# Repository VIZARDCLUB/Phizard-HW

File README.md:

# Phizard-HW

The Phizard board is licensed under CERN Open Hardware Licence Version 2 - Strongly Reciprocal.  
This means that any changes made to the board should be made public and CHANGES.txt be updated to reflect said changes.  

The Phizard Link-V board is licensed under GPL-3.0 licence.  

Phizard has some added features based on PhobGCC 2.0.5.  
Currently works with [PhoZL](https://github.com/sean44104/PhoZL) firmware.  

# CHANGES.txt
- Original pad footprint for ABXY. Support 2pin DIP switches. Added holes for D2LS switches.  
- Original pad footprint for D-pad. Support SMD tact switches, D2LS switches and 2pin DIP switches.  
- Added thin tactile switch support to the START button.  
- Swap USB connecter to USB-C.  
- Added ZL button connected to GPIO12. Works with PhoZL firmware.  
- Fixed the Z/ZL footprint to fit right angle mouse switches.  
- Added breakout pad for Dup and Dleft for SoreiruFactory's Double LR Trigger.
- Added a 22ohm resister and a pad for 3.3V cell rumble.  
- Added Phizard Link-V based on OlyU-V. This supports Phob vision output. (I will make an adapter for it in the future.)
- PH connector can be used for LR pad without shell trimming

# Parts example
[H5.2mm Square micro switch](https://a.aliexpress.com/_on09e08) for ABXY and D-pad  
[D2LS-11](https://mou.sr/3ILtBsM) and the other switches that uses the same footprint for ABXY and Dpad  
[SKRRAAE010](https://mou.sr/3PtAZNg) and GBASP start button rubber for start (The edited shell will be published after tested)  

# Credit
## Main board
https://github.com/PhobGCC/PhobGCCv2-HW  
https://github.com/sean44104/phozl  

## USB features
https://github.com/Crane1195/Model-U  
https://github.com/sean44104/OlyU  
https://github.com/rana-sylvatica/OlyU-V

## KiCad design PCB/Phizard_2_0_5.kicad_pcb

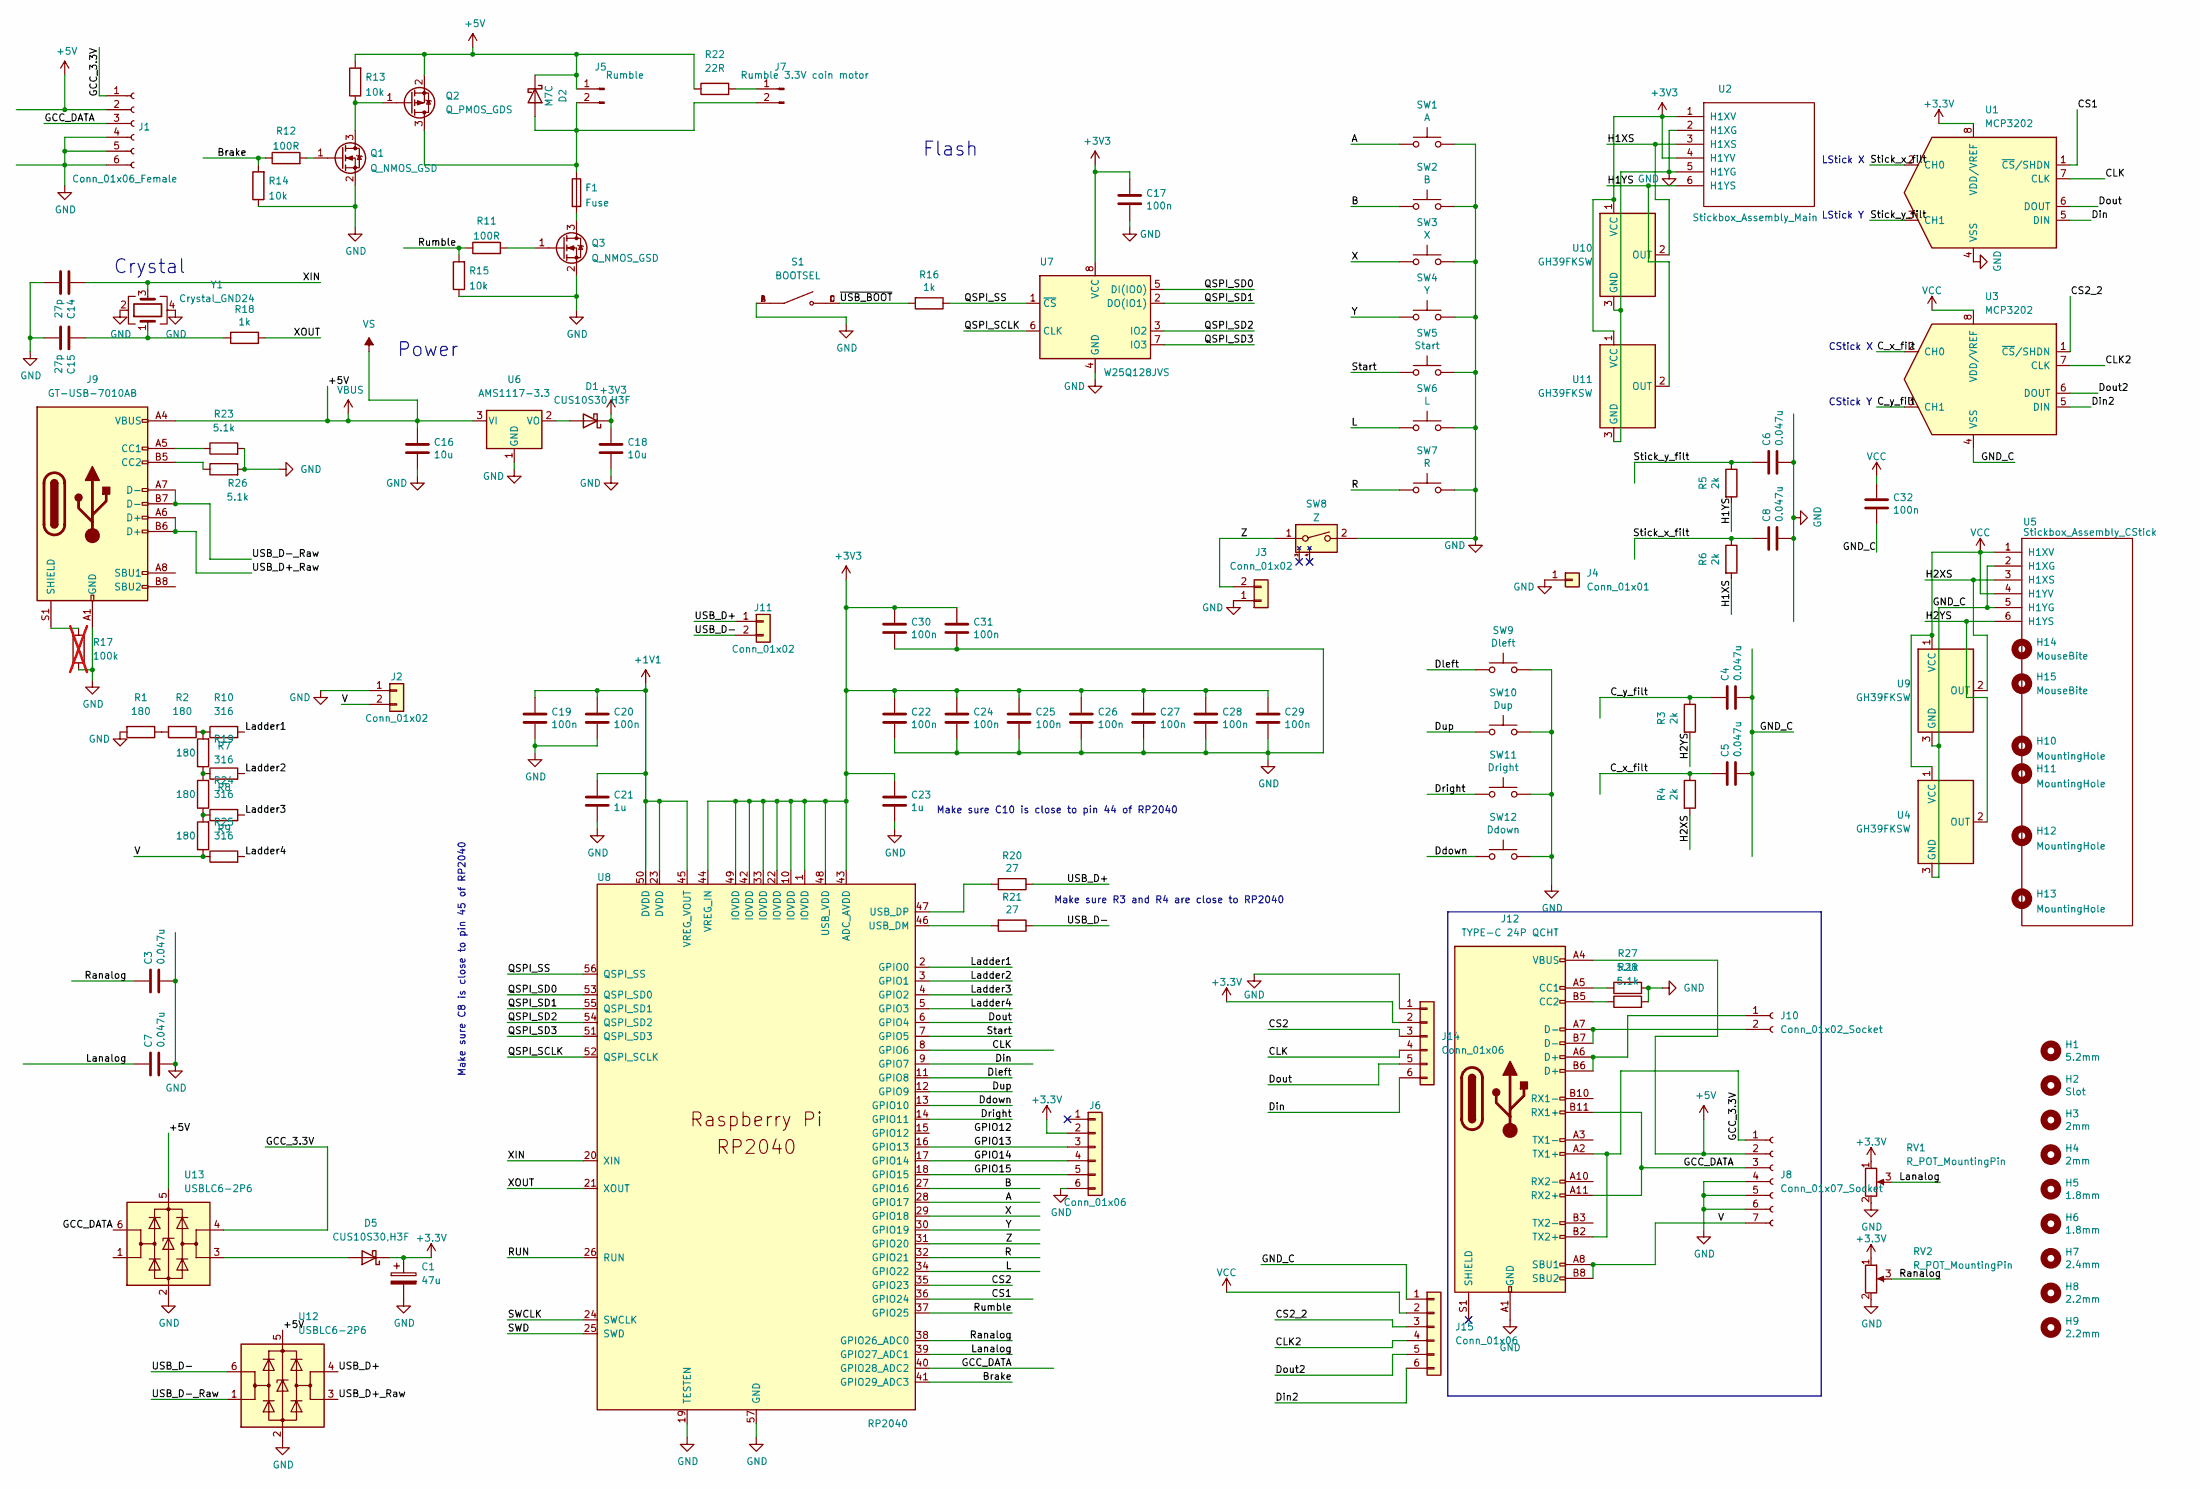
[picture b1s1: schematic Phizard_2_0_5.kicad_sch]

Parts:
C1: 47u; CP_EIA-3528-12_Kemet-T_Pad1.50x2.35mm_HandSolder; LCSC C136751
C3, C4, C5, C6, C7, C8: 0.047u; C_0603_HandSoldering; LCSC C1622
C14, C15: 27p; C_0402_1005Metric; LCSC C1557
C16, C18: 10u; C_0805_2012Metric; LCSC C15850
C17, C19, C20, C22, C24, C25, C26, C27, C28, C29, C30, C31, C32: 100n; C_0402_1005Metric; LCSC C1525
C21, C23: 1u; C_0402_1005Metric; LCSC C52923
D1, D5: CUS10S30,H3F; D_SOD-323; LCSC C146335
D2: M7C; D_SOD-123; LCSC C8598
F1: Fuse; Fuse_1206_3216Metric; LCSC C69680
H1: 5.2mm; MountingHole_5.2mm
H2: Slot
H3, H4: 2mm; MountingHole_2.0mm
H5, H6: 1.8mm; MountingHole_1.8mm
H7: 2.4mm; MountingHole_2.4mm
H8, H9: 2.2mm; MountingHole_2.2mm
H10: MountingHole; MountingHole_1.8mm
H11: MountingHole; MountingHole_5.2mm
H12, H13: MountingHole; MountingHole_2.0mm
H14: MouseBite; breakaway-mousebites-double-v2-small
H15: MouseBite; breakaway-mousebites-double-v2-large
J1: Conn_01x06_Female; GCC_Header_Straight_1x06_Pitch2.00mm
J2, J11: Conn_01x02; PinHeader_1x02_P2.00mm_Vertical
J3: Conn_01x02; PinHeader_1x02_P2.00mm_Horizontal
J4: Conn_01x01; PinHeader_1x01_P2.54mm_Vertical
J5: Rumble; rumble_pins
J6, J14, J15: Conn_01x06; PinSocket_1x06_P2.00mm_Vertical
J7: Rumble 3.3V coin motor; rumble_pins
J8: Conn_01x07_Socket
J9: GT-USB-7010AB; USB_C_Receptacle_G-Switch_GT-USB-7010ASV; LCSC C963412
J10: Conn_01x02_Socket
J12: TYPE-C 24P QCHT; LCSC C456013
Q1, Q3: Q_NMOS_GSD; SOT-23; LCSC C20917
Q2: Q_PMOS_GDS; SOT-23; LCSC C15127
R1, R2, R7, R8, R9: 180; R_0402_1005Metric; LCSC C38941
R3, R4, R5, R6: 2k; R_0603_1608Metric_Pad0.98x0.95mm_HandSolder; LCSC C22975
R10, R19, R24, R25: 316; R_0402_1005Metric; LCSC C159037
R11, R12: 100R; R_0603_1608Metric_Pad0.98x0.95mm_HandSolder; LCSC C22775
R13, R14, R15: 10k; R_0603_1608Metric_Pad0.98x0.95mm_HandSolder; LCSC C25804
R16, R18: 1k; C_0402_1005Metric; LCSC C11702
R17: 100k; R_0603_1608Metric_Pad0.98x0.95mm_HandSolder; LCSC C25803; not fitted
R20, R21: 27; C_0402_1005Metric; LCSC C25100
R22: 22R; R_1206_3216Metric; LCSC C2845146
R23, R26, R27, R28: 5.1k; R_0402_1005Metric; LCSC C105872
RV1, RV2: R_POT_MountingPin; GCC_Slider
S1: BOOTSEL; SW_TS-1187A-B-A-B; PARTREV A0; LCSC C318884
SW1: A; ABXY_Contact_Omron_Switch_Circley
SW2: B; ABXY_Contact_Omron_Switch_Circley
SW3: X; ABXY_Contact_Omron_Switch_Circley
SW4: Y; ABXY_Contact_Omron_Switch_Circley
SW5: Start; Start_Contact
SW6: L; Pin_Header_Straight_1x02_Pitch2.54mm
SW7: R; Pin_Header_Straight_1x02_Pitch2.54mm
SW8: Z; Z_Switch_Edge_Omron
SW9: Dleft; Dpad_Contact_TL3315NF_2_ZigZag
SW10: Dup; Dpad_Contact_TL3315NF_2_ZigZag
SW11: Dright; Dpad_Contact_TL3315NF_2_ZigZag
SW12: Ddown; Dpad_Contact_TL3315NF_2_ZigZag
U1, U3: MCP3202; SOIC-8_3.9x4.9mm_P1.27mm; LCSC C56997
U2: Stickbox_Assembly_Main; GCC_Stickbox_Hall_Only
U4, U9, U10, U11: GH39FKSW; SOT-23; LCSC C266128
U5: Stickbox_Assembly_CStick; GCC_Stickbox_Hall_Only
U6: AMS1117-3.3; SOT-223-3_TabPin2; LCSC C6186
U7: W25Q128JVS; SOIC-8_5.23x5.23mm_P1.27mm; LCSC C97521
U8: RP2040; RP2040-QFN-56; LCSC C2040
U12, U13: USBLC6-2P6; SOT-666; LCSC C2827693
Y1: Crystal_GND24; Crystal_SMD_3225-4Pin_3.2x2.5mm; LCSC C403945

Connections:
+1V1: C19.1, C20.1, C21.1, U8.23 (DVDD), U8.45 (VREG_VOUT), U8.50 (DVDD)
+5V: C16.1, D2.1 (K), J1.2, J5.1, J8.2, J9.A4 (VBUS), J9.A9 (VBUS), J9.B4 (VBUS), J9.B9 (VBUS), J12.A4 (VBUS), J12.A9 (VBUS), J12.B4 (VBUS), J12.B9 (VBUS), Q2.2 (S), R13.2, R22.1, U6.3 (VI), U12.5 (VBUS), U13.5 (VBUS)
/A: SW1.1, U8.28 (GPIO17)
/B: SW2.1, U8.27 (GPIO16)
/Brake: R12.1, R14.2, U8.41 (GPIO29_ADC3)
/CLK: J14.4, U1.7 (CLK), U8.8 (GPIO6)
/CLK2: J15.4, U3.7 (CLK)
/CS1: U1.1 (~CS/SHDN), U8.36 (GPIO24)
/CS2: J14.3, U8.35 (GPIO23)
/CS2_2: J15.3, U3.1 (~CS/SHDN)
/C_x_filt: C5.1, R4.1, U3.2 (CH0)
/C_y_filt: C4.1, R3.1, U3.3 (CH1)
/Ddown: SW12.1, SW12.3, SW12.5, U8.13 (GPIO10)
/Din: J14.6, U1.5 (DIN), U8.9 (GPIO7)
/Din2: J15.6, U3.5 (DIN)
/Dleft: SW9.1, SW9.3, SW9.5, U8.11 (GPIO8)
/Dout: J14.5, U1.6 (DOUT), U8.6 (GPIO4)
/Dout2: J15.5, U3.6 (DOUT)
/Dright: SW11.1, SW11.3, SW11.5, U8.14 (GPIO11)
/Dup: SW10.1, SW10.3, SW10.5, U8.12 (GPIO9)
/GCC_3.3V: J1.1, J8.1, J12.A2 (TX1+), J12.B2 (TX2+), U13.4 (I/O2)
/GCC_DATA: J1.3, J8.3, J12.A11 (RX2+), J12.B11 (RX1+), U8.40 (GPIO28_ADC2), U13.6 (I/O1)
/GND_C: C4.2, C5.2, C32.2, J15.1, U3.4 (VSS), U4.3 (GND), U5.2 (H1XG), U5.5 (H1YG), U9.3 (GND)
/GPIO12: U8.15 (GPIO12); also elsewhere on the board
/GPIO13: J6.3, U8.16 (GPIO13)
/GPIO14: J6.4, U8.17 (GPIO14)
/GPIO15: J6.5, U8.18 (GPIO15)
/H1XS: R6.2, U2.3 (H1XS), U10.2 (OUT)
/H1YS: R5.2, U2.6 (H1YS), U11.2 (OUT)
/H2XS: R4.2, U5.3 (H1XS), U9.2 (OUT)
/H2YS: R3.2, U4.2 (OUT), U5.6 (H1YS)
/L: SW6.1, U8.34 (GPIO22)
/Ladder1: R10.2, U8.2 (GPIO0)
/Ladder2: R19.2, U8.3 (GPIO1)
/Ladder3: R24.2, U8.4 (GPIO2)
/Ladder4: R25.2, U8.5 (GPIO3)
/Lanalog: C7.1, RV1.3 (Signal), U8.39 (GPIO27_ADC1)
/QSPI_SCLK: U7.6 (CLK), U8.52 (QSPI_SCLK)
/QSPI_SD0: U7.5 (DI(IO0)), U8.53 (QSPI_SD0)
/QSPI_SD1: U7.2 (DO(IO1)), U8.55 (QSPI_SD1)
/QSPI_SD2: U7.3 (IO2), U8.54 (QSPI_SD2)
/QSPI_SD3: U7.7 (IO3), U8.51 (QSPI_SD3)
/QSPI_SS: R16.1, U7.1 (~CS), U8.56 (QSPI_SS)
/R: SW7.1, U8.32 (GPIO21)
/RUN: U8.26 (RUN)
/Ranalog: C3.1, RV2.3 (Signal), U8.38 (GPIO26_ADC0)
/Rumble: R11.1, R15.2, U8.37 (GPIO25)
/SWCLK: U8.24 (SWCLK)
/SWD: U8.25 (SWD)
/Start: SW5.1, U8.7 (GPIO5)
/Stick_x_filt: C8.1, R6.1, U1.2 (CH0)
/Stick_y_filt: C6.1, R5.1, U1.3 (CH1)
/USB_D+_Raw: J9.A6 (D+), J9.B6 (D+), U12.3 (I/O2)
/USB_D-_Raw: J9.A7 (D-), J9.B7 (D-), U12.1 (I/O1)
/V: J1.7, J2.2, J8.7, J12.A8 (SBU1), J12.B8 (SBU2), R9.1, R25.1
/X: SW3.1, U8.29 (GPIO18)
/XIN: C14.1, U8.20 (XIN), Y1.3
/XOUT: R18.1, U8.21 (XOUT)
/Y: SW4.1, U8.30 (GPIO19)
/Z: J3.2, SW8.1, U8.31 (GPIO20)
/~USB_BOOT: R16.2, S1.C, S1.D
GND: C1.2, C3.2, C6.2, C7.2, C8.2, C14.2, C15.2, C16.2, C17.2, C18.2, C19.2, C20.2, C21.2, C22.2, C23.2, C24.2, C25.2, C26.2, C27.2, C28.2, C29.2, C30.2, C31.2, J1.4, J1.5, J1.6, J2.1, J3.1, J4.1, J6.6, J8.4, J8.5, J8.6, J9.A1 (GND), J9.A12 (GND), J9.B1 (GND), J9.B12 (GND), J12.A1 (GND), J12.A12 (GND), J12.B1 (GND), J12.B12 (GND), J14.1, Q1.2 (S), Q3.2 (S), R1.2, R14.1, R15.1, R17.2, R23.2, R26.2, R27.2, R28.2, RV1.2 (GND), RV2.2 (GND), S1.A, S1.B, SW1.2, SW2.2, SW3.2, SW4.2, SW5.2, SW6.2, SW7.2, SW8.2, SW9.2, SW9.4, SW9.6, SW10.2, SW10.4, SW10.6, SW11.2, SW11.4, SW11.6, SW12.2, SW12.4, SW12.6, U1.4 (VSS), U2.2 (H1XG), U2.5 (H1YG), U6.1 (GND), U7.4 (GND), U8.19 (TESTEN), U8.57 (GND), U10.3 (GND), U11.3 (GND), U12.2 (GND), U13.2 (GND), Y1.2, Y1.4; also elsewhere on the board
unnamed: C15.1, R18.2, Y1.1
unnamed: D1.2 (A), U6.2 (VO)
unnamed: D2.2 (A), F1.1, J5.2, J7.2, Q2.3 (D)
unnamed: D5.2 (A), U13.3 (I/O2)
unnamed: J7.1, R22.2
unnamed: J9.A5 (CC1), R23.1
unnamed: J9.B5 (CC2), R26.1
unnamed: J9.S1 (SHIELD), R17.1
unnamed: J12.A5 (CC1), R27.1
unnamed: J12.B5 (CC2), R28.1
unnamed: Q1.3 (D), Q2.1 (G), R13.1
unnamed: Q1.1 (G), R12.2
unnamed: F1.2, Q3.3 (D)
unnamed: Q3.1 (G), R11.2
unnamed: R1.1, R2.2
unnamed: R2.1, R7.2, R10.1
unnamed: R7.1, R8.2, R19.1
unnamed: R8.1, R9.2, R24.1
unnamed: R21.2, U8.46 (USB_DM)
unnamed: R20.2, U8.47 (USB_DP)
VCC: C32.1, J15.2, U3.8 (VDD/VREF), U4.1 (VCC), U5.1 (H1XV), U5.4 (H1YV), U9.1 (VCC)

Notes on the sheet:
Power
LStick Y
Make sure C10 is close to pin 44 of RP2040
CStick Y
Make sure R3 and R4 are close to RP2040
Make sure C8 is close to pin 45 of RP2040
Flash
Crystal
CStick X
LStick X

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
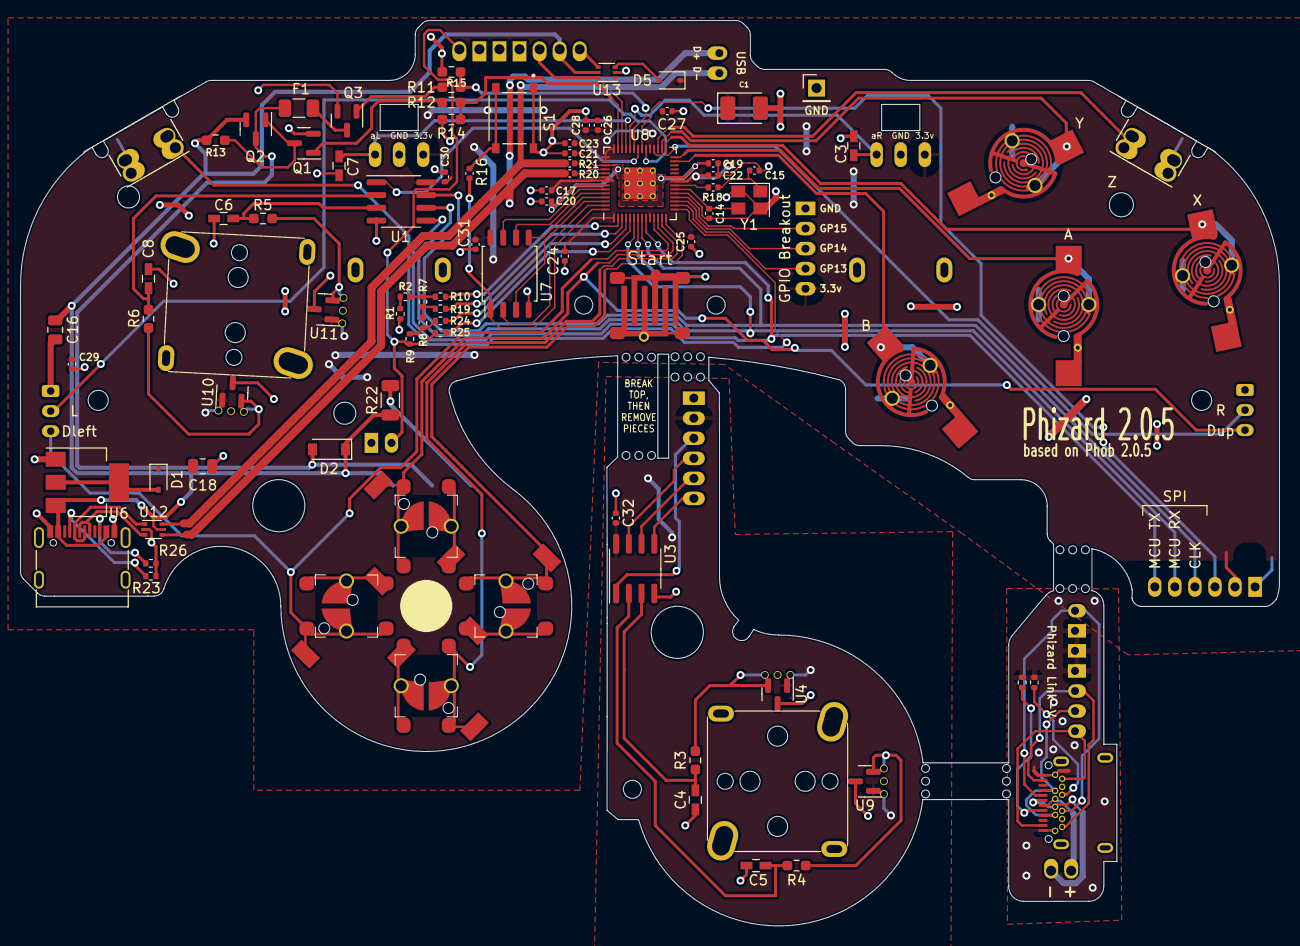
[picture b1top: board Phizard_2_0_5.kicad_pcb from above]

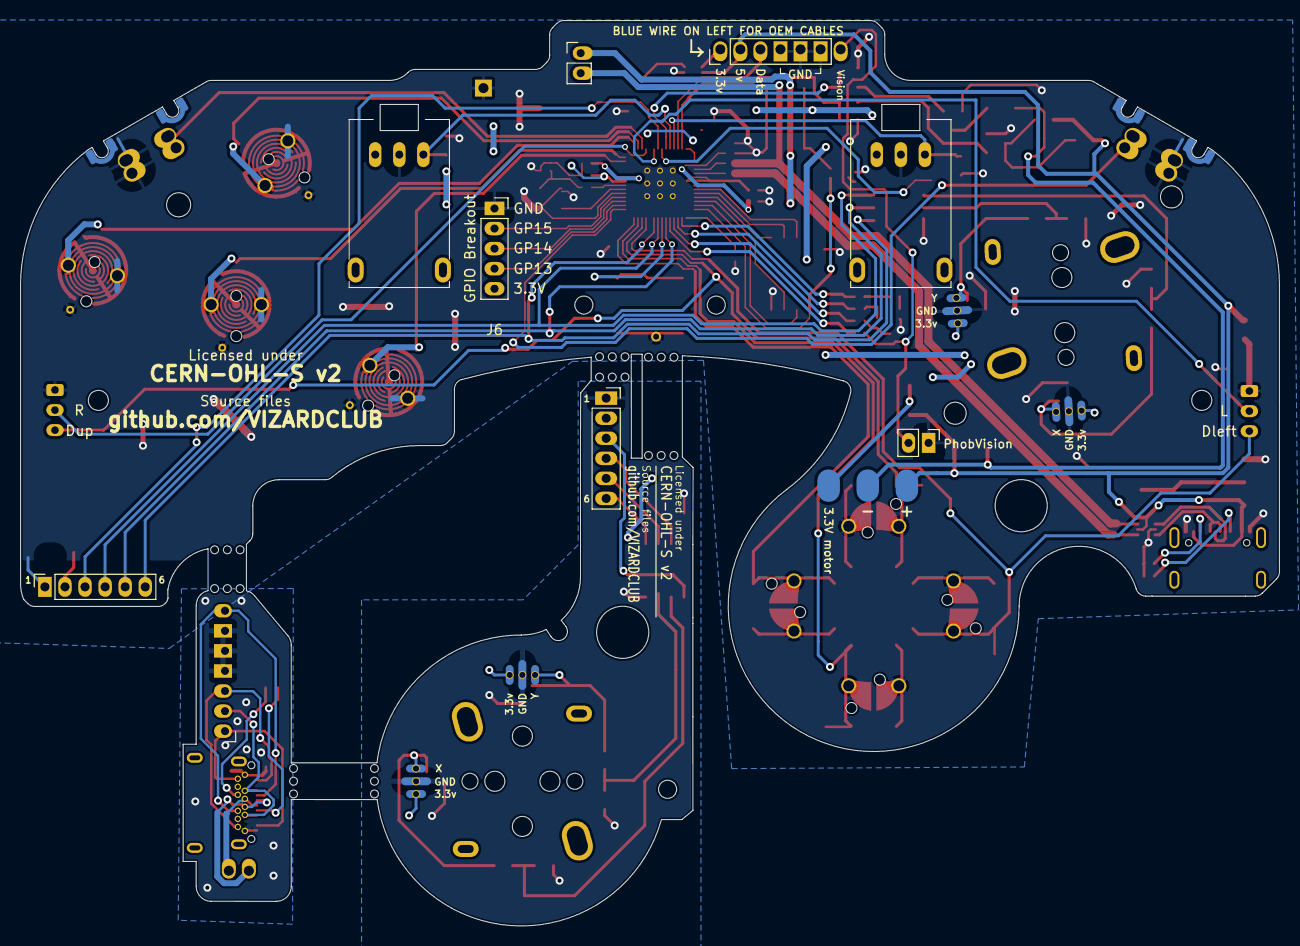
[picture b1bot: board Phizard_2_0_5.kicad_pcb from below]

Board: 2 copper layers, 125.5 x 90.3 mm, 122 parts (13 on the bottom side), 82 nets.

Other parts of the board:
H14#2, H14#3, H14#4, H14#5: MouseBite; breakaway-mousebites-double-v2-small
SW8#2: Z; Z_Switch_Edge_Omron

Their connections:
/GPIO12: SW8#2.2; also elsewhere on the board
GND: SW8#2.1; also elsewhere on the board

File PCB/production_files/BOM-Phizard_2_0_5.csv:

Comment,Designator,Footprint,LCSC
5.1k,"R23,R26,R27,R28",R_0402_1005Metric,C105872
1k,"R16,R18",C_0402_1005Metric,C11702
47u,C1,CP_EIA-3528-12_Kemet-T_Pad1.50x2.35mm_HandSolder,C136751
"CUS10S30,H3F","D1,D5",D_SOD-323,C146335
Q_PMOS_GDS,Q2,SOT-23,C15127
100n,"C17,C19,C20,C22,C24,C25,C26,C27,C28,C29,C30,C31,C32",C_0402_1005Metric,C1525
27p,"C14,C15",C_0402_1005Metric,C1557
10u,"C16,C18",C_0805_2012Metric,C15850
316,"R10,R19,R24,R25",R_0402_1005Metric,C159037
0.047u,"C3,C4,C5,C6,C7,C8",C_0603_HandSoldering,C1622
RP2040,U8,RP2040-QFN-56,C2040
Q_NMOS_GSD,"Q1,Q3",SOT-23,C20917
100R,"R11,R12",R_0603_1608Metric_Pad0.98x0.95mm_HandSolder,C22775
2k,"R3,R4,R5,R6",R_0603_1608Metric_Pad0.98x0.95mm_HandSolder,C22975
27,"R20,R21",C_0402_1005Metric,C25100
10k,"R13,R14,R15",R_0603_1608Metric_Pad0.98x0.95mm_HandSolder,C25804
DRV5055A3xDBZxQ1,"U10,U11,U4,U9",SOT-23,C266128
USBLC6-2P6,"U12,U13",SOT-666,C2827693
22R,R22,R_1206_3216Metric,C2845146
BOOTSEL,S1,SW_TS-1187A-B-A-B,C318884
180,"R1,R2,R7,R8,R9",R_0402_1005Metric,C38941
Crystal_GND24,Y1,Crystal_SMD_3225-4Pin_3.2x2.5mm,C403945
USB_C_Receptacle,J12,Shou Han Type-C 24P QCHT,C456013
1u,"C21,C23",C_0402_1005Metric,C52923
MCP3202,"U1,U3",SOIC-8_3.9x4.9mm_P1.27mm,C56997
AMS1117-3.3,U6,SOT-223-3_TabPin2,C6186
Fuse,F1,Fuse_1206_3216Metric,C69680
M7C,D2,D_SOD-123,C8598
USB_C_Receptacle_USB2.0,J9,USB_C_Receptacle_G-Switch_GT-USB-7010ASV,C963412
W25Q128JVS,U7,SOIC-8_5.23x5.23mm_P1.27mm,C97521

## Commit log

2024-02-21 Create Phizard
2024-03-04 Update README.md
    added known issues
2024-03-20 Add JLCPCB production files
    add JLCPCB production files
    bug fixes

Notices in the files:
PCB/Phizard_2_0_5.kicad_pcb:
CERN-OHL-S v2
